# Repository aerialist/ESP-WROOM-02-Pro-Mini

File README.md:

# ESP-WROOM-02-Pro-Mini
This is yet another ESP-WROOM-02 breakout.

Warning: This hasn't been fabricated or tested yet.

Design intentions are:

* Use ESP-WROOM-02 so that it can be used in Japan with TELEC cetification.
* It would fit to Adafruit Feather Wing product line.
* Remove serial-to-USB conversion circuit to reduce cost and save space.
* Keep uUSB connector for powering the device.
* Battery connector is optional and moved to the backside to save space.
* LiPo charging circuit is optional.

ESP-WROOM-02 eagle library is taken from
https://github.com/ikesato/eagle-libraries/blob/master/lbr/esp-wroom-02.lbr

The design is derived from Adafruit-Huzzah-ESP8266-Basic-Breakout-PCB and Adafruit-Feather-ESP8266-HUZZAH-PCB. Please find the copy of original readme attached below.

# Adafruit-Huzzah-ESP8266-Basic-Breakout-PCB
PCB files for Adafruit Huzzah ESP8266 Basic Breakout

Format is EagleCAD schematic and board layout

For more details, check out the product page at

-----> http://www.adafruit.com/products/2471

Adafruit invests time and resources providing this open source design, 
please support Adafruit and open-source hardware by purchasing 
products from Adafruit!

Designed by Adafruit Industries.  
Creative Commons Attribution, Share-Alike license, check license.txt for more information
All text above must be included in any redistribution

# Adafruit-Feather-ESP8266-HUZZAH-PCB
PCB files for the Adafruit Feather ESP8266 HUZZAH

Format is EagleCAD schematic and board layout

For more details, check out the product page at

  * https://www.adafruit.com/product/2821

Adafruit invests time and resources providing this open source design, 
please support Adafruit and open-source hardware by purchasing 
products from Adafruit!

Designed by Adafruit Industries.  
Creative Commons Attribution, Share-Alike license, check license.txt for more information
All text above must be included in any redistribution

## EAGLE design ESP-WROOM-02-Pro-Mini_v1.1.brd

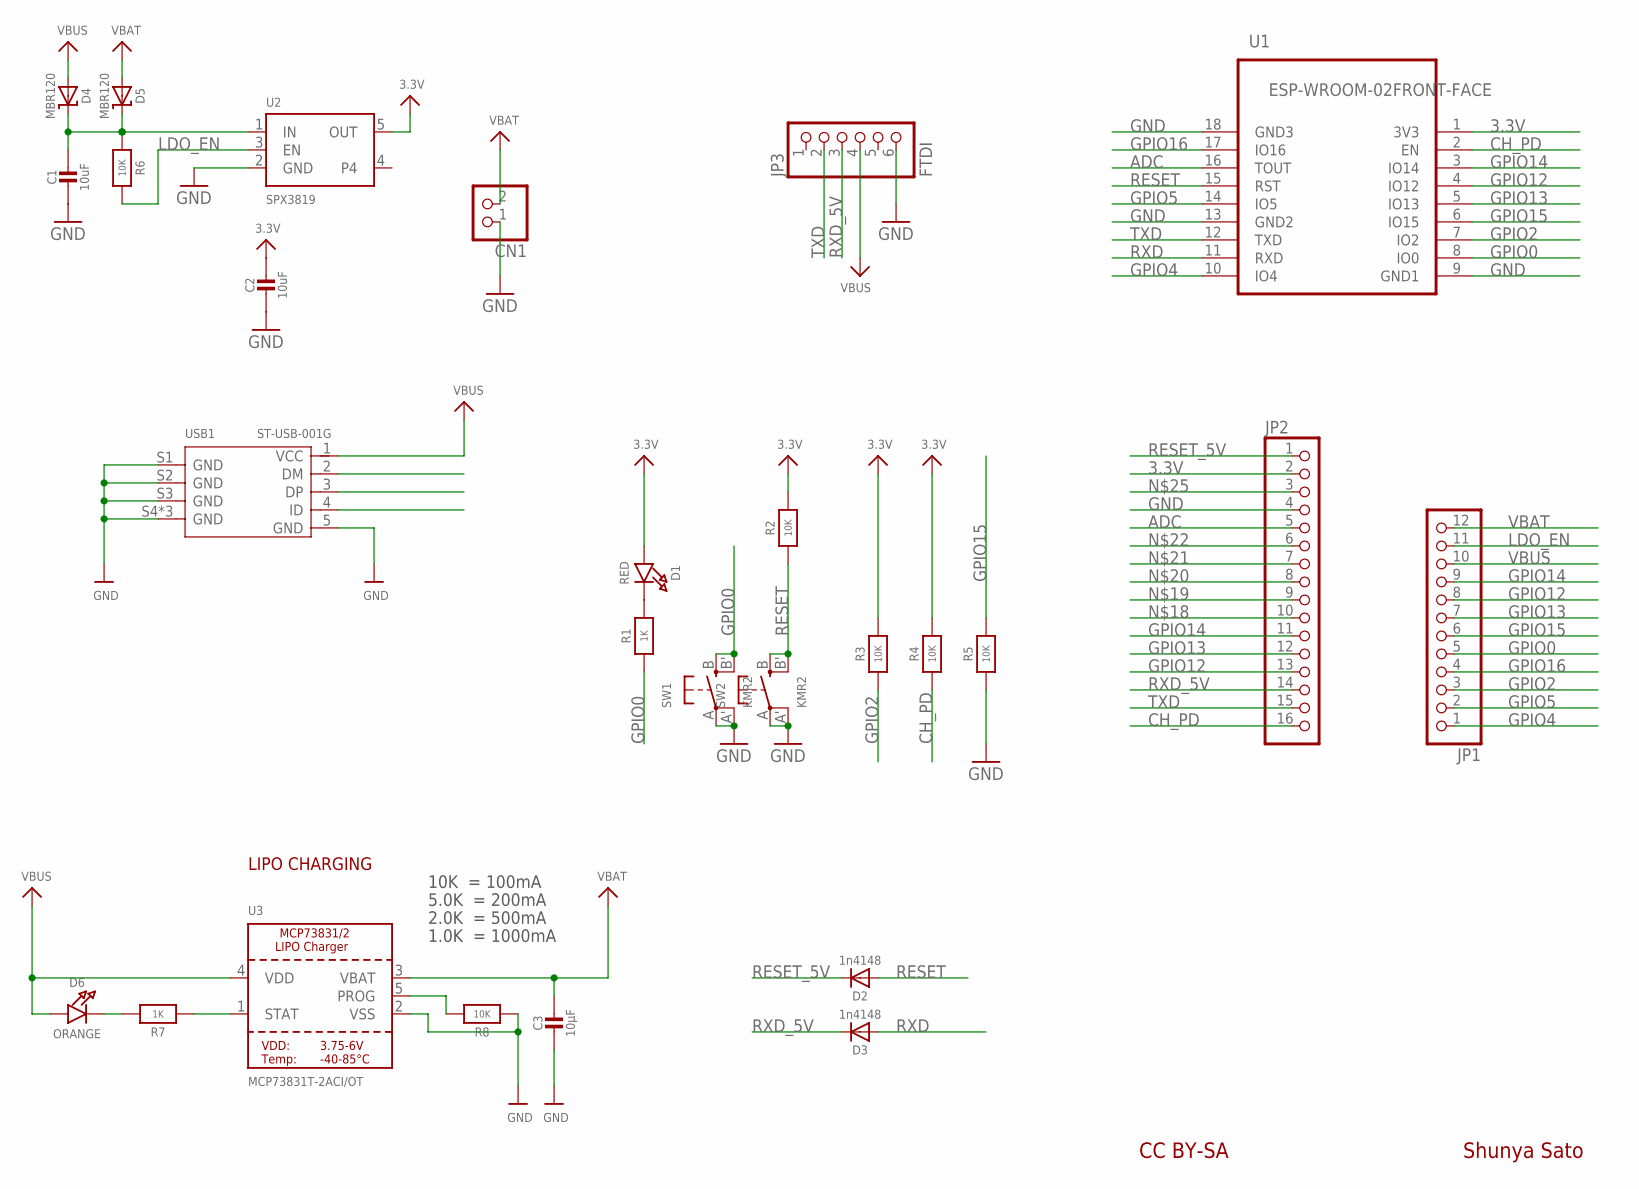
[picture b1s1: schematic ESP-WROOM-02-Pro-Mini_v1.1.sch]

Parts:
C1, C2: 10uF; 0805-NO
C3: 10µF; 0805-NO
CN1: JST_2PIN; JSTPH2
D1: RED; CHIPLED_0805_NOOUTLINE
D2, D3: 1n4148; SOD-323
D4, D5: MBR120; SOD-123
D6: ORANGE; CHIPLED_0805_NOOUTLINE
JP1: PINHD-1X12-CB; 1X12-CB
JP2: HEADER-1X16ROUND; 1X16_ROUND
JP3: FTDI; 1X06_ROUND_70
R1, R7: 1K; 0805-NO
R2, R3, R4, R5, R6, R8: 10K; 0805-NO
SW1, SW2: KMR2; BTN_KMR2_4.6X2.8
U1: ESP-WROOM-02FRONT-FACE; FRONT-FACE
U2: SPX3819; SOT23-5
U3: MCP73831T-2ACI/OT; SOT23-5
USB1: ST-USB-001G; MICRO-USB5+4P-SMD-0.65-B

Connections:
3.3V: C2.1, D1.A, JP2.2, R2.2, R3.2, R4.2, U1.1 (3V3), U2.5 (OUT)
ADC: JP2.5, U1.16 (TOUT)
CH_PD: JP2.16, R4.1, U1.2 (EN)
GND: C1.2, C2.2, C3.2, CN1.1, JP2.4, JP3.6, R5.1, R8.1, SW1.A, SW1.A' (P1), SW2.A, SW2.A' (P1), U1.9 (GND1), U1.13 (GND2), U1.18 (GND3), U2.2 (GND), U3.2 (VSS), USB1.5 (GND), USB1.S1 (GND), USB1.S2 (GND), USB1.S3 (GND), USB1.S4 (GND), USB1.S5 (GND), USB1.S6 (GND)
GPIO0: JP1.5, R1.1, SW1.B (S), SW1.B' (S1), U1.8 (IO0)
GPIO2: JP1.3, R3.1, U1.7 (IO2)
GPIO4: JP1.1, U1.10 (IO4)
GPIO5: JP1.2, U1.14 (IO5)
GPIO12: JP1.8, JP2.13, U1.4 (IO12)
GPIO13: JP1.7, JP2.12, U1.5 (IO13)
GPIO14: JP1.9, JP2.11, U1.3 (IO14)
GPIO15: JP1.6, R5.2, U1.6 (IO15)
GPIO16: JP1.4, U1.17 (IO16)
LDO_EN: JP1.11, R6.2, U2.3 (EN)
unnamed: D6.C, R7.2
unnamed: R7.1, U3.1 (STAT)
unnamed: C1.1, D4.C, D5.C, R6.1, U2.1 (IN)
unnamed: D1.C, R1.2
unnamed: R8.2, U3.5 (PROG)
RESET: D2.A, R2.1, SW2.B (S), SW2.B' (S1), U1.15 (RST)
RESET_5V: D2.C, JP2.1
RXD: D3.A, U1.11 (RXD)
RXD_5V: D3.C, JP2.14, JP3.3
TXD: JP2.15, JP3.2, U1.12 (TXD)
VBAT: C3.1, CN1.2, D5.A, JP1.12, U3.3 (VBAT)
VBUS: D4.A, D6.A, JP1.10, JP3.4, U3.4 (VDD), USB1.1 (VCC)

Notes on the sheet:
10K = 100mA
5.0K = 200mA
2.0K = 500mA
1.0K = 1000mA
LIPO CHARGING
Shunya Sato
CC BY-SA

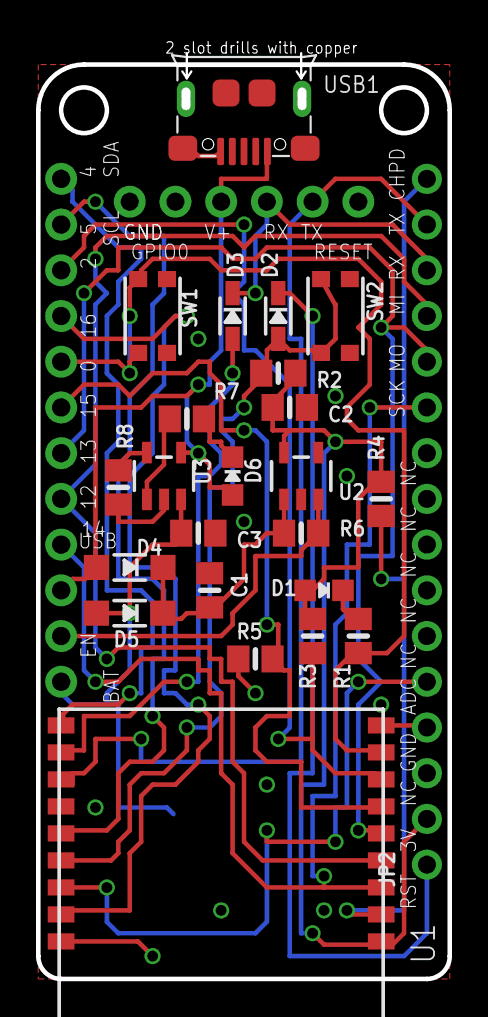
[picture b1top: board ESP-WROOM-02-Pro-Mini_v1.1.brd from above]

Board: 2 copper layers, 22.6 x 52.0 mm, 27 parts (1 on the bottom side), 26 nets.

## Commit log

2016-05-07 Add pdf and png of schematics and layout
2016-05-14 Add citation for ESP-WROOM-02 eagle library.

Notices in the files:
parts and their libraries:
microbuilder: This work is placed in the public domain, and may be freely used for commercial and non-commercial work with the following conditions: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
